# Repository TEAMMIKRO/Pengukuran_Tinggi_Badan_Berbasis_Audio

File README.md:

.png)

Alat pengukur tinggi badan dengan output suara adalah sebuah perangkat yang menggunakan mikrokontroler ATmega2560 dan sensor ultrasonik untuk mengukur tinggi badan secara akurat, sambil memberikan umpan balik melalui suara yang telah direkam sebelumnya. Alat pengukur tinggi badan berbasis ATmega2560 ini dirancang untuk memberikan pengalaman interaktif dan ramah pengguna, terutama bagi tuna rungu. Menggunakan sensor ultrasonik untuk mengukur tinggi badan, alat ini memberikan output yang telah direkam sebelumnya. Buzzer dan LED digunakan sebagai indikator status dan hasil pengukuran, sementara push button memulai atau mengulangi proses pengukuran. Hasil pengukuran ditampilkan pada layar, memastikan pengguna mendapatkan informasi secara visual.

WORKSHOP MIKROKONTROLLER - [PROGRAM STUDI TEKNIK ELEKTRONIKA](https://elektronika.pens.ac.id/) - [POLITEKNIK ELEKTRONIKA NEGERI SURABAYA](https://www.pens.ac.id/)

`DOSEN PENGAMPU : Akhmad Hendriawan ST, MT`

`NIP. 197501272002121003`

`TEAM DAN PEMBAGIAN TUGAS`

NO| NAMA                               | NRP          |JOBDESK + TUGAS TAMBAHAN
--| -----------------------------------|--------------|--------------
1.| Devani Febecca Virgina Sudaryono   | 2122500002   | Project Manager + pembelian komponen
2.| Syahrir Nur                        | 2122500005   | Hardware Developer + membantu publikasi melalui github + Pembuatan Flyer dan Poster
3.| Igna Wahyu Bahyaqi                 | 2122500007   | Hardware Developer + membantu pemrograman arduino 
4.| Bagus Dwi Kurniawan                | 2122500019   | 3D Designer + membantu proses perakitan dan soldering
5.| Atilla Habil Prakoso               | 2122500028   | Software Developer + membantu proses perakitan dan soldering
6.| Arief Naufaldi                     | 2122500031   | Documentation 

## Daftar Isi

- [Komponen Yang Digunakan](https://github.com/TEAMMIKRO/Pengukuran_Tinggi_Badan_Berbasis_Audio/blob/main/README.md#komponen-yang-digunakan)
- [Blok Diagram](https://github.com/TEAMMIKRO/Pengukuran_Tinggi_Badan_Berbasis_Audio/blob/main/README.md#blok-diagram)
- [Konsep Simulasi](https://github.com/TEAMMIKRO/Pengukuran_Tinggi_Badan_Berbasis_Audio/blob/main/README.md#konsep-simulasi)
- [Skematik Rangkaian](https://github.com/TEAMMIKRO/Pengukuran_Tinggi_Badan_Berbasis_Audio/blob/main/README.md#skematik-rangkaian)
- [Desain Shield PCB](https://github.com/TEAMMIKRO/Pengukuran_Tinggi_Badan_Berbasis_Audio/blob/main/README.md#desain-shield-pcb)
- [Desain 3D](https://github.com/TEAMMIKRO/Pengukuran_Tinggi_Badan_Berbasis_Audio/blob/main/README.md#desain-3d)
- [Audio Project](https://github.com/TEAMMIKRO/Pengukuran_Tinggi_Badan_Berbasis_Audio/blob/main/README.md#audio-project)
- [Website & Database](https://github.com/TEAMMIKRO/Pengukuran_Tinggi_Badan_Berbasis_Audio/blob/main/README.md#website--database)
- [Program](https://github.com/TEAMMIKRO/Pengukuran_Tinggi_Badan_Berbasis_Audio/blob/main/README.md#website--database)
- [Dokumentasi Kegiatan](https://github.com/TEAMMIKRO/Pengukuran_Tinggi_Badan_Berbasis_Audio/blob/main/README.md#dokumentasi)
- [Tutorial Upload Foto dan Vidio di Readme Github](https://github.com/TEAMMIKRO/Pengukuran_Tinggi_Badan_Berbasis_Audio/blob/main/README.md#tutorial-upload-foto-dan-vidio-di-readme-github)
- [Hasil Project](https://github.com/TEAMMIKRO/Pengukuran_Tinggi_Badan_Berbasis_Audio/blob/main/README.md#hasil)

## Komponen Yang Digunakan

NO| Komponen                           | Jumlah       
--| -----------------------------------|--------------
1.| Arduino ATMEGA2560                 | 1   
2.| Sensor Ultrasonik (HC-SR04)        | 1  
3.| Speaker                            | 1  
4.| LCD 128x32                         | 1 
5.| IC PAM8403                         | 1 
6.| Push Button                        | 1 
7.| LED 3mm                            | 2
8.| PCB                                | 1
9.| Resistor 220ohm                    | 2
10.| Resistor 10kohm                   | 1

## Blok Diagram

Alat pengukuran tinggi badan berbasis ATmega2560 dengan output suara adalah alat yang mengukur tinggi badan seseorang menggunakan sensor ultrasonik yang terhubung ke mikrokontroler ATmega2560. Berikut prinsip kerjanya :

1. **Sensor Pengukuran**: Sensor yang digunakan untuk mengukur tinggi badan berupa sensor ultrasonik yang mengukur jarak dari sensor ke permukaan atas kepala seseorang.

2. **Pemrosesan Mikrokontroler**: Data yang diterima dari sensor diproses oleh mikrokontroler ATmega2560. Mikrokontroler ini memiliki berbagai pin input/output yang dapat digunakan untuk berkomunikasi dengan sensor dan juga untuk mengontrol output suara.

3. **Perhitungan Tinggi Badan**: Data yang diterima dari sensor diolah oleh mikrokontroler untuk menghitung tinggi badan. Misalnya, pada sensor ultrasonik, waktu yang dibutuhkan untuk pantulan gelombang suara bisa diubah menjadi jarak.

4. **Output Suara**: Setelah tinggi badan dihitung, mikrokontroler mengirimkan instruksi ke speaker yang terhubung, untuk menghasilkan suara yang memberitahu pengguna tentang tinggi badan yang terukur. Suara ini bisa berupa angka yang diucapkan, misalnya "Tinggi badan Anda adalah 170 centimeter", atau sinyal bunyi yang memberi tahu bahwa pengukuran telah selesai. Serta akan ditampilkan melalui LCD

5. **Suara Prosedur Penggunaan**: Alat ini juga dapat menggunakan suara untuk memberikan petunjuk kepada pengguna tentang cara menggunakan alat dengan benar. Misalnya, suara tersebut dapat memberi instruksi seperti "Silakan berdiri tegak".

6. **Output Suara Berdasarkan Proses**: Selain itu, alat ini juga dapat menggunakan suara untuk memberikan umpan balik langsung kepada pengguna selama proses pengukuran. Misalnya, alat ini dapat mengucapkan "Pengukuran sedang berlangsung, mohon tunggu sebentar" atau "Pengukuran selesai, tinggi badan Anda adalah...".

## Konsep Simulasi
Berikut adalah skematik breadboard untuk simulasi menggunakan wokwi yang disimulasikan dengan arduino uno

Dengan hasil simulasi seperti ditunjukkan pada video berikut: 

https://github.com/TEAMMIKRO/Pengukuran_Tinggi_Badan_Berbasis_Audio/assets/168399446/19a3157d-1056-4a39-92ac-d9e758f5ff1c

Template simulasi dapat diperoleh dan didownload melalui link [berikut](https://wokwi.com/projects/399474799840596993) 

## Skematik Rangkaian
Berikut ini adalah hasil skematik rangkaian sistem pendeteksi tinggi badan berbasis audio menggunakan software KiCad

Untuk semua file yang dibutuhkan terkait skematik rangkaian dapat diakses melalui link [berikut](https://github.com/TEAMMIKRO/Pengukuran_Tinggi_Badan_Berbasis_Audio/tree/01fa1884fd218f2bfc27fa47c7c2f433bcaae3b4/PCB%20Board)

## Desain Shield PCB

Tutorial pembuatan desain PCB sebagai berikut :

https://github.com/TEAMMIKRO/Pengukuran_Tinggi_Badan_Berbasis_Audio/assets/168399446/bc3afa7e-2291-4080-a7c7-66f3c7525a5d

## Desain 3D
Berikut ini adalah hasil [desain 3D](https://github.com/TEAMMIKRO/Pengukuran_Tinggi_Badan_Berbasis_Audio/tree/275d552436e7006e9d67db9b5f6c3f620f8418e4/Desain%203D)

1. Desain 3D Casing

.PNG)
   
2. Desain 3D Casing + Komponen
   
.PNG)

3. Desain Keseluruhan Alat

.PNG)

4. Desain 3D PCB dengan komponen

5. Desain 3D PCB tanpa Komponen

## Informasi Penempatan Komponen Pada PCB
Tata letak penempatan komponen pada PCB untuk memudahkan dalam proses perakitan adalah seperti gambar berikut :

## Manufaktur Desain Casing
Berikut adalah detail ukuran casing untuk kebutuhan manufaktur :

## Audio Project
Pada project pengukuran tinggi badan, Terdapat 5 mode [audio](https://github.com/TEAMMIKRO/Pengukuran_Tinggi_Badan_Berbasis_Audio/tree/01fa1884fd218f2bfc27fa47c7c2f433bcaae3b4/Project%20Audio) sebagai bentuk perintah cara penggunaan alat serta tinggi badan yang terukur 
1. Audio Selamat Datang

.PNG)

.jpeg)

.jpeg)

Vidio perbedaan audio sebelum dan sesudah diedit menggunakan audacity adalah sebagai berikut :

https://github.com/TEAMMIKRO/Pengukuran_Tinggi_Badan_Berbasis_Audio/assets/168399446/1ca87a29-002d-49de-8172-6b7dc6da22cd

2. Audio Instruksi 1

.jpeg)

.jpeg)

.jpeg)

Vidio perbedaan audio sebelum dan sesudah diedit menggunakan audacity adalah sebagai berikut :

https://github.com/TEAMMIKRO/Pengukuran_Tinggi_Badan_Berbasis_Audio/assets/168399446/b0740aec-1e81-46ea-bcb6-a836326b6d8a

3. Audio Instruksi 2

.jpeg)

.jpeg)

.jpeg)

Vidio perbedaan audio sebelum dan sesudah diedit menggunakan audacity adalah sebagai berikut :

https://github.com/TEAMMIKRO/Pengukuran_Tinggi_Badan_Berbasis_Audio/assets/168399446/71092118-cb9e-4144-a3ec-47b7ac19b7bf

4. Audio Tinggi Badan

.jpeg)

.jpeg)

.jpeg)

Vidio perbedaan audio sebelum dan sesudah diedit menggunakan audacity adalah sebagai berikut :

https://github.com/TEAMMIKRO/Pengukuran_Tinggi_Badan_Berbasis_Audio/assets/168399446/f88d98dd-6304-464c-ac30-c74001f160de

5. Audio Sampai Jumpa

.jpeg)

.jpeg)

.jpeg)

Vidio perbedaan audio sebelum dan sesudah diedit menggunakan audacity adalah sebagai berikut :

https://github.com/TEAMMIKRO/Pengukuran_Tinggi_Badan_Berbasis_Audio/assets/168399446/b0327692-7e0e-4e4d-8a4f-5353cc58cd45

Berikut ini merupakan  tutorial cara mengedit vidio di audacity beserta cara konvert audio format MP3 to HEX 

https://github.com/TEAMMIKRO/Pengukuran_Tinggi_Badan_Berbasis_Audio/assets/168399446/0aed3fbb-e3ae-4b80-bbc8-792d36571a03

## Website & Database

1. Database

2. Website

## Dokumentasi

1. Pembuatan Simulasi Melalui Software

2. Desain PCB

3. Desain 3D

4. Soldering Awal

5. Pembuatan Web/database
6. Pembuatan Program Mikrokontroler
7. Pembuatan Audio

8. Perakitan Keseluruhan Alat

9. Publikasi Github

10. Percobaan Alat

## Tutorial Upload Foto dan Vidio di Readme Github

Tutorial upload foto dan vidio pada readme github sebagai berikut :

https://github.com/TEAMMIKRO/Pengukuran_Tinggi_Badan_Berbasis_Audio/assets/168399446/a2bcb10a-18a6-4992-a28e-b74a7d9fbc8a

https://github.com/TEAMMIKRO/Pengukuran_Tinggi_Badan_Berbasis_Audio/assets/168399446/8b76bbaa-6051-4535-83ba-0f69c84c6a65

10. Percobaan Alat

## Hasil

1. Cetak PCB

2. Cetak Akrilik

3. Keseluruhan Alat

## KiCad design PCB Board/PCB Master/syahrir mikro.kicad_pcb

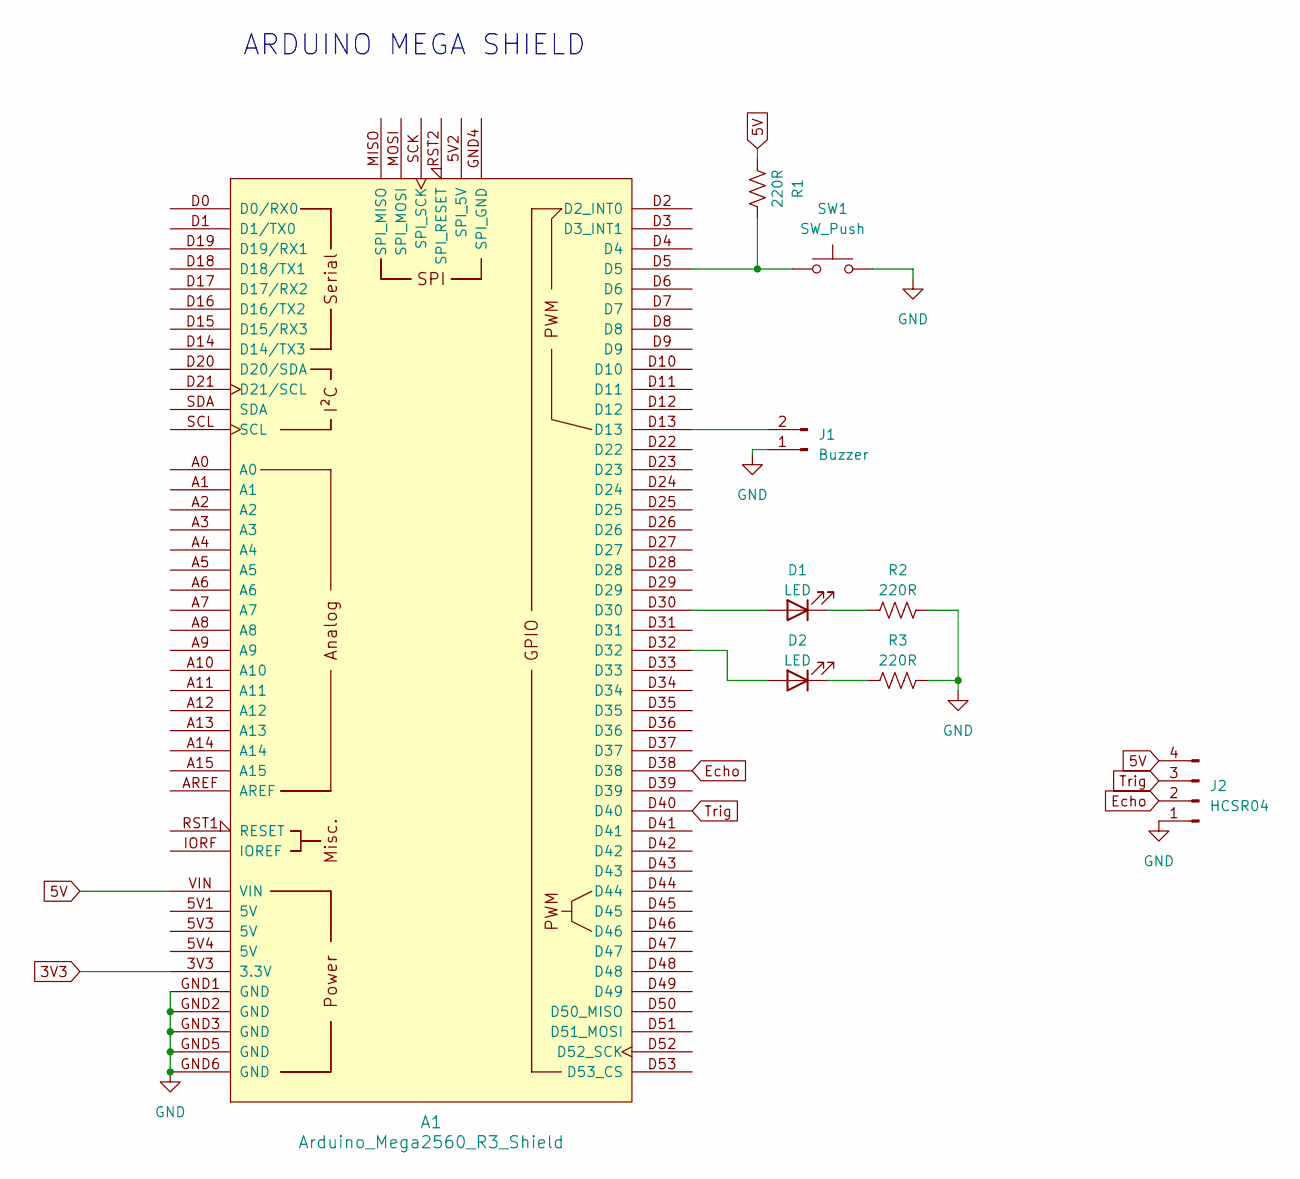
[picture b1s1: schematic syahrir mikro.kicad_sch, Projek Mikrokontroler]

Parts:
A1: Arduino_Mega2560_R3_Shield
D1, D2: LED; LED_D5.0mm
J1: Buzzer; PinHeader_1x02_P2.54mm_Vertical
J2: HCSR04; PinHeader_1x04_P2.54mm_Vertical
R1, R2, R3: 220R; R_Axial_DIN0207_L6.3mm_D2.5mm_P10.16mm_Horizontal
SW1: SW_Push; SW_PUSH_6mm_H8mm

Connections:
3V3: A1.3V3 (3.3V)
5V: A1.VIN, J2.4, R1.1
Echo: A1.D38, J2.2
GND: A1.GND1 (GND), A1.GND2 (GND), A1.GND3 (GND), A1.GND5 (GND), A1.GND6 (GND), J1.1, J2.1, R2.2, R3.2, SW1.1
unnamed: A1.D5, R1.2, SW1.2
unnamed: A1.D30, D1.2 (A)
unnamed: D1.1 (K), R2.1
unnamed: A1.D32, D2.2 (A)
unnamed: D2.1 (K), R3.1
unnamed: A1.D13, J1.2
Trig: A1.D40, J2.3

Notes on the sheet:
ARDUINO MEGA SHIELD

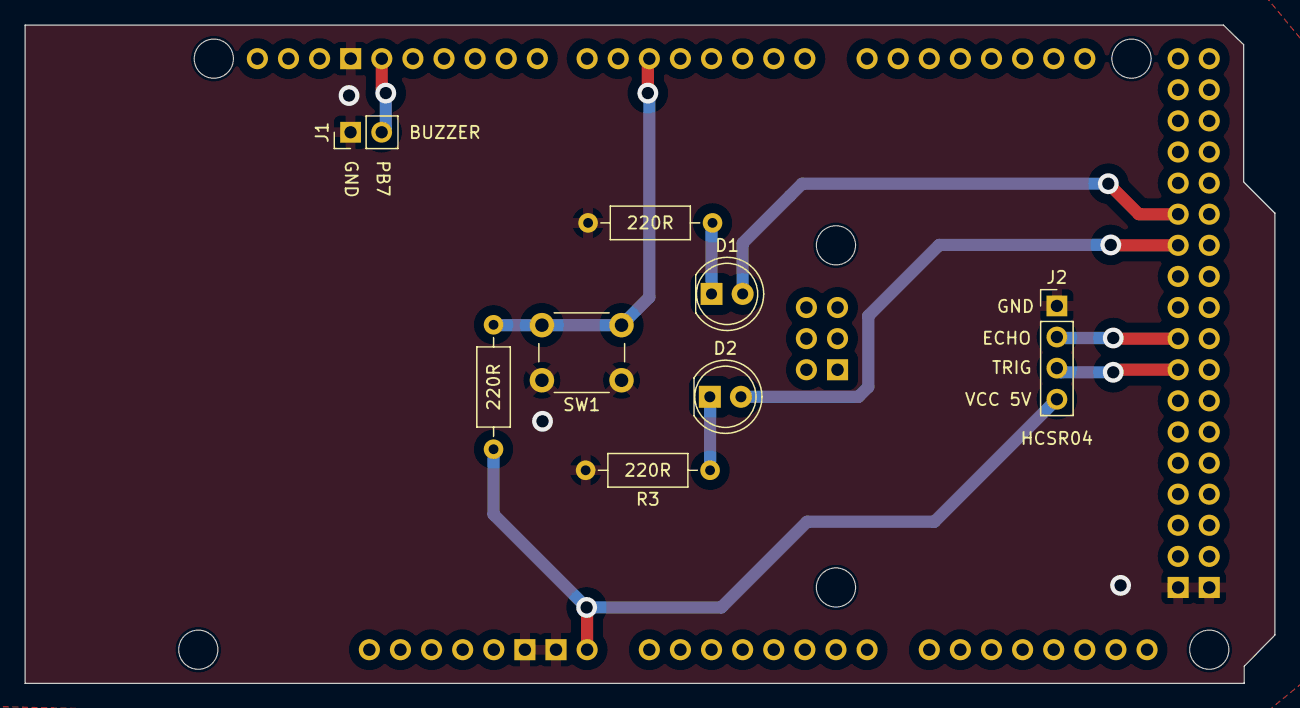
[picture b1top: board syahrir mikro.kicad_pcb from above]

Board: 2 copper layers, 102.0 x 53.8 mm, 9 parts (0 on the bottom side), 10 nets.

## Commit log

2024-05-20 Create PCB Board
2024-05-26 Create desainpcb
2024-05-26 Create Program Simulasi Audio
2024-05-26 Create Audio Project
2024-05-26 Create Audio_Project
2024-05-26 Create Audio Selamat Datang
2024-05-26 Create Assets
2024-05-26 Create emptyfile
